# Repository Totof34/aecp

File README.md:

aecp
====

The project describes a electronic mapped car ignition
especialy for Panhard two cylindre

If you would have more information about this project please visit 
www.audiyofan.org

A link to the dedicated post 
http://www.audiyofan.org/forum/viewtopic.php?f=71&t=9221

PCB & schema are designed with Kicad

**********************************
*A new version called V4 in 2025*
**********************************

The new board in 2025

For the Gerber's file see the folder "aecp/source_kicad/gerber V4/"

all PCB Gerber files and 3D printing files from version 2025 grouped in the folder "aecp/manufacturing_files"

*******************************************************************

the new board uses a Atmega328 and usb link or a bluetooth module ( HC-05 or 06 )
to transmit some data to the PC

it's a Arduino Nano_V3

The idea comes from this site
http://a110a.free.fr/SPIP172/plan.php3

with this startpoint

And finally with a Nano V3.0 with a dedicated page here
http://a110a.free.fr/SPIP172/article.php3?id_article=142

But this project have some child too for exemple 
https://github.com/michelm63/AEMM
with a dedicated post here
http://motos-anglaises.com/phpBB3/viewtopic.php?f=3&t=28953

All the things we need is on this picture for the hardware,
and a car of course to use it !!

The prototype of the new board under construction and under kicad

With some parts 

The new version of the PCB for longtime test

You can select different curve with a box

To develop our electronic ignition, we create an new interface with a Nano_V3
to receive data from the Atmega328 and visualize the centrifugal advance curves and vacuum advance

This interface is designed under Processing IDE and the board is programmed with Arduino IDE
All the files available in subfolders

For the printed circuit board please see the source_kicad folder 
or the build folder for a made version

For the schema see below

for the rest, I suggest you to navigate into folders and open the pdf

The main code is explained through comments ( in French) in the ino file ( see Arduino folder )

Enjoy

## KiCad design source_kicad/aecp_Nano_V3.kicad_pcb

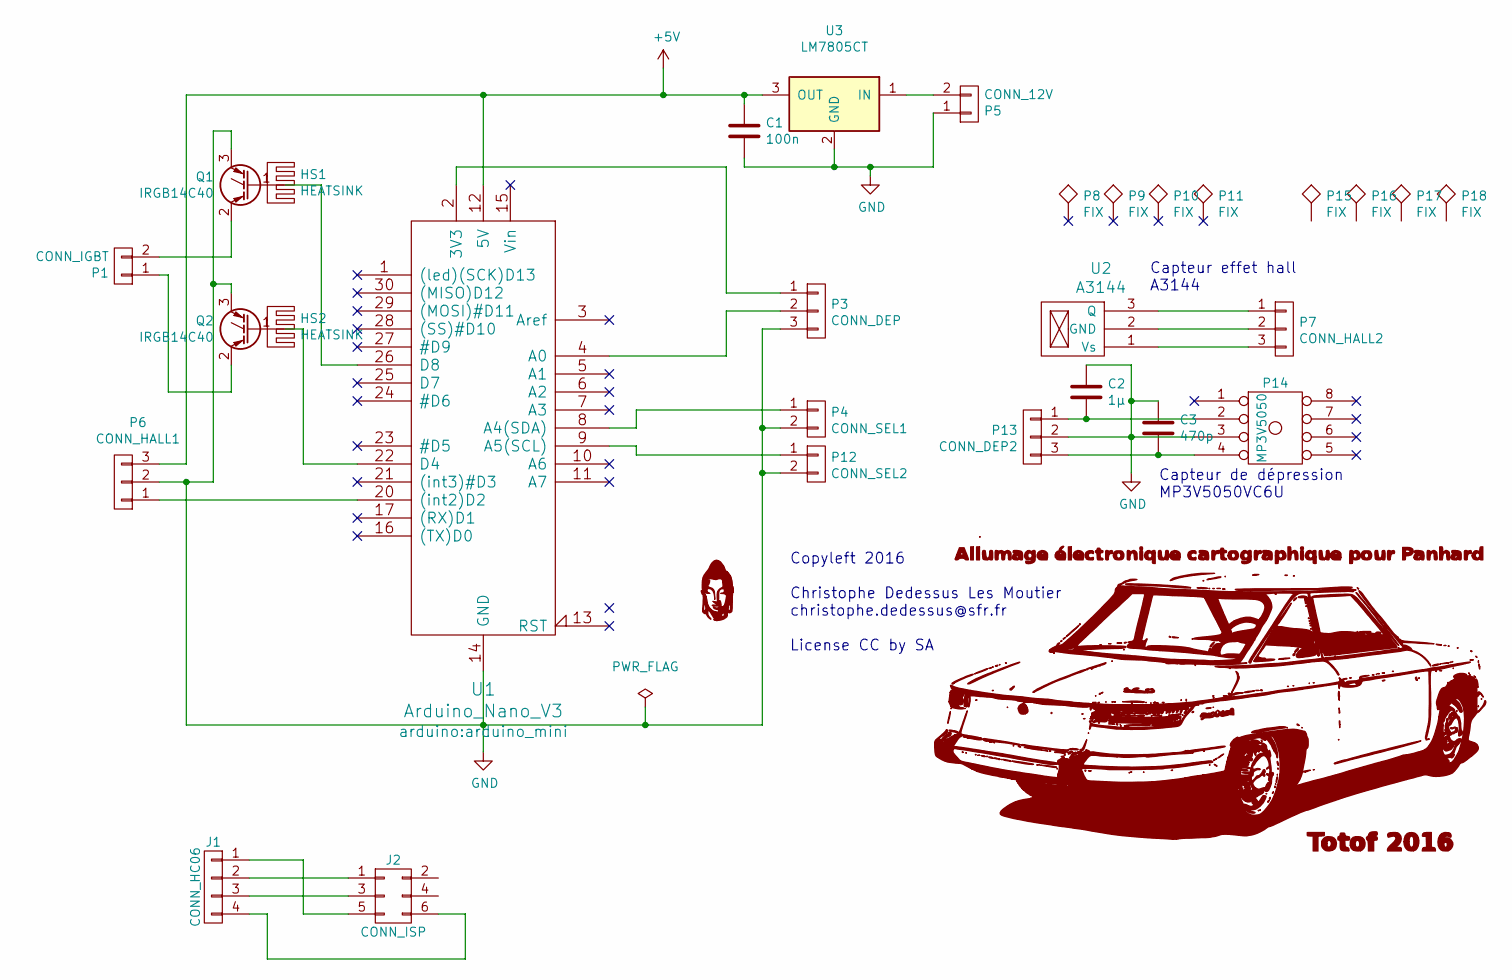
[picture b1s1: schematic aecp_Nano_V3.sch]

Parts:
C1: 100n; C_Rect_L7_W3.5_P5
C2: 1µ; C_Rect_L7_W3.5_P5
C3: 470p; C_Rect_L7_W3.5_P5
G1: Tete_budha
G2: 24CT; Panhard24CT
HS1, HS2: HEATSINK; Heatsink_Fischer_SK104-STC-STIC_35x13mm_2xDrill2.5mm
J1: CONN_HC06; pin_strip_4
J2: CONN_ISP; pin_strip_3x2
P1: CONN_IGBT; bornier2
P3: CONN_DEP; bornier3
P4: CONN_SEL1; bornier2
P5: CONN_12V; bornier2
P6: CONN_HALL1; bornier3
P7: CONN_HALL2; Socket_Strip_Straight_1x03
P8, P9, P10, P11: FIX; 1pin
P12: CONN_SEL2; bornier2
P13: CONN_DEP2; Socket_Strip_Straight_1x03
P14: MP3V5050; MP3V5050V
P15, P16, P17, P18: FIX; MountingHole_2.2mm_M2_Pad_Via
Q1, Q2: IRGB14C40; TO-220_Neutral123_Vertical_LargePads
U1: Arduino_Nano_V3; arduino_mini
U2: A3144; TO-92_Horizontal2_Inline_Narrow_Oval
U3: LM7805CT; TO-220_Neutral123_Vertical_LargePads

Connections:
+5V: C1.1, P6.3, U1.12 (5V), U3.3 (OUT)
GND: C1.2, C2.1, C3.1, P3.3, P4.2, P5.1, P6.2, P12.2, P13.2, P14.3, Q1.3 (E), Q2.3 (E), U1.14 (GND), U1.19 (GND), U3.2 (GND)
unnamed: C2.2, P13.1, P14.2
unnamed: C3.2, P13.3, P14.4
unnamed: J1.1, J2.5
unnamed: J1.2, J2.1
unnamed: J1.3, J2.3
unnamed: J1.4, J2.6
unnamed: P1.1, Q2.2 (C)
unnamed: P1.2, Q1.2 (C)
unnamed: P3.1, U1.2 (3V3)
unnamed: P3.2, U1.4 (A0)
unnamed: P4.1, U1.8 (A4(SDA))
unnamed: P5.2, U3.1 (IN)
unnamed: P6.1, U1.20 ((int2)D2)
unnamed: P7.1, U2.3 (Q)
unnamed: P7.2, U2.2 (GND)
unnamed: P7.3, U2.1 (Vs)
unnamed: P12.1, U1.9 (A5(SCL))
unnamed: Q1.1 (G), U1.26 (D8)
unnamed: Q2.1 (G), U1.22 (D4)

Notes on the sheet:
Copyleft 2016 Christophe Dedessus Les Moutier christophe.dedessus@sfr.fr License CC by SA
Capteur de dépression MP3V5050VC6U
Capteur effet hall A3144

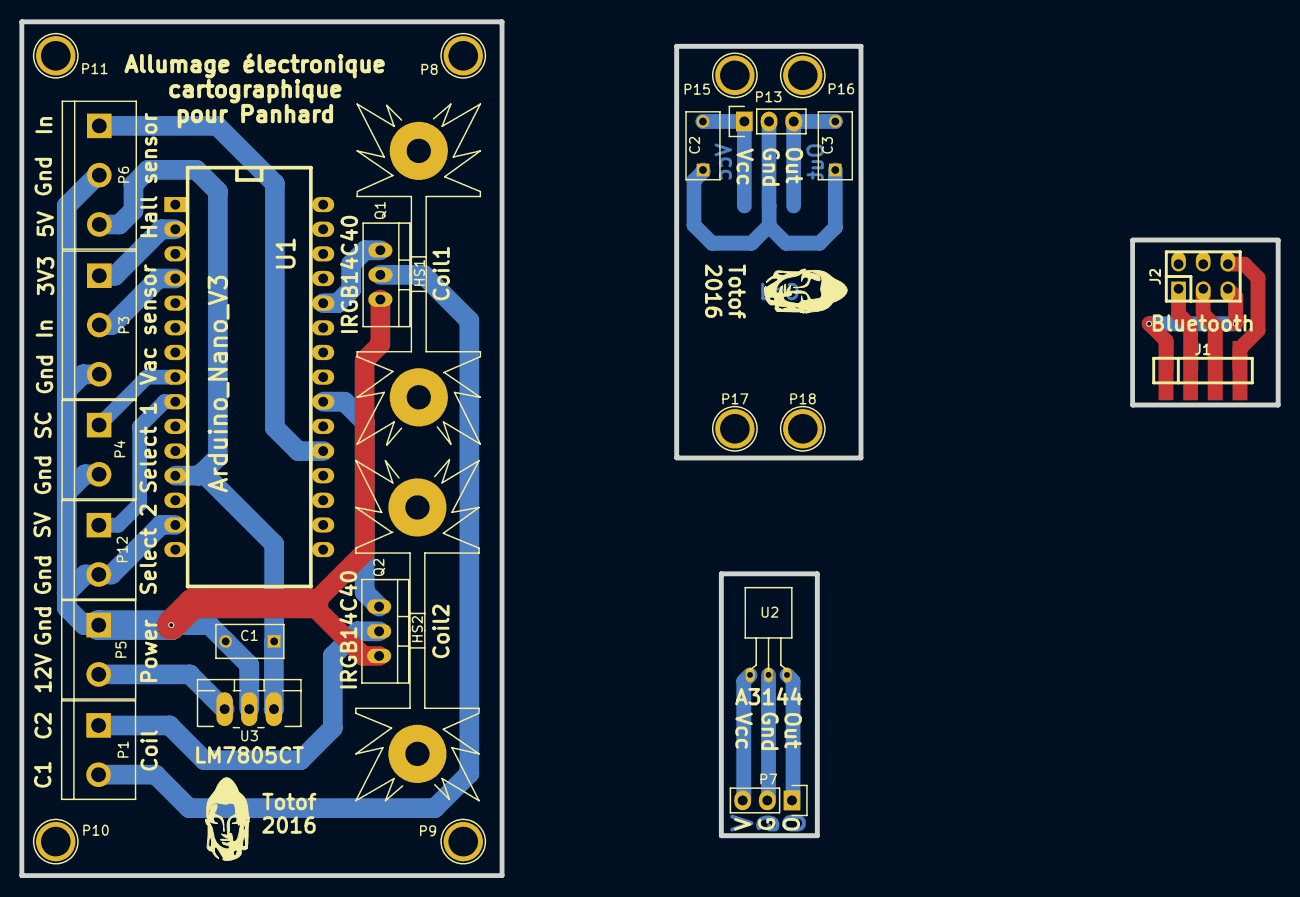
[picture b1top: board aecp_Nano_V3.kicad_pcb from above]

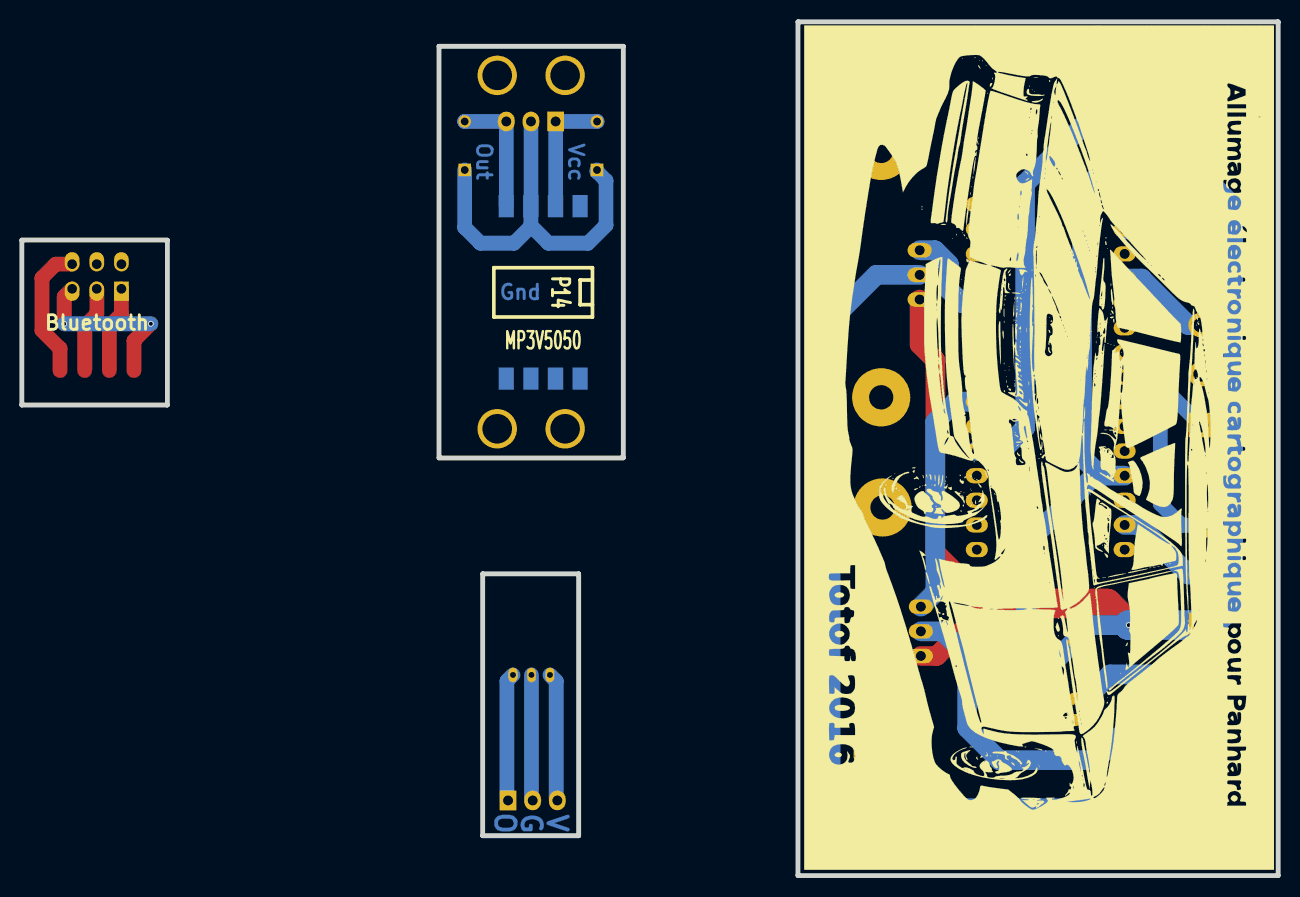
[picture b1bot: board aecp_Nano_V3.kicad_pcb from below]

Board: 2 copper layers, 129.5 x 88.0 mm, 32 parts (2 on the bottom side), 21 nets.

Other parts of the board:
G1#2: Tete_budha

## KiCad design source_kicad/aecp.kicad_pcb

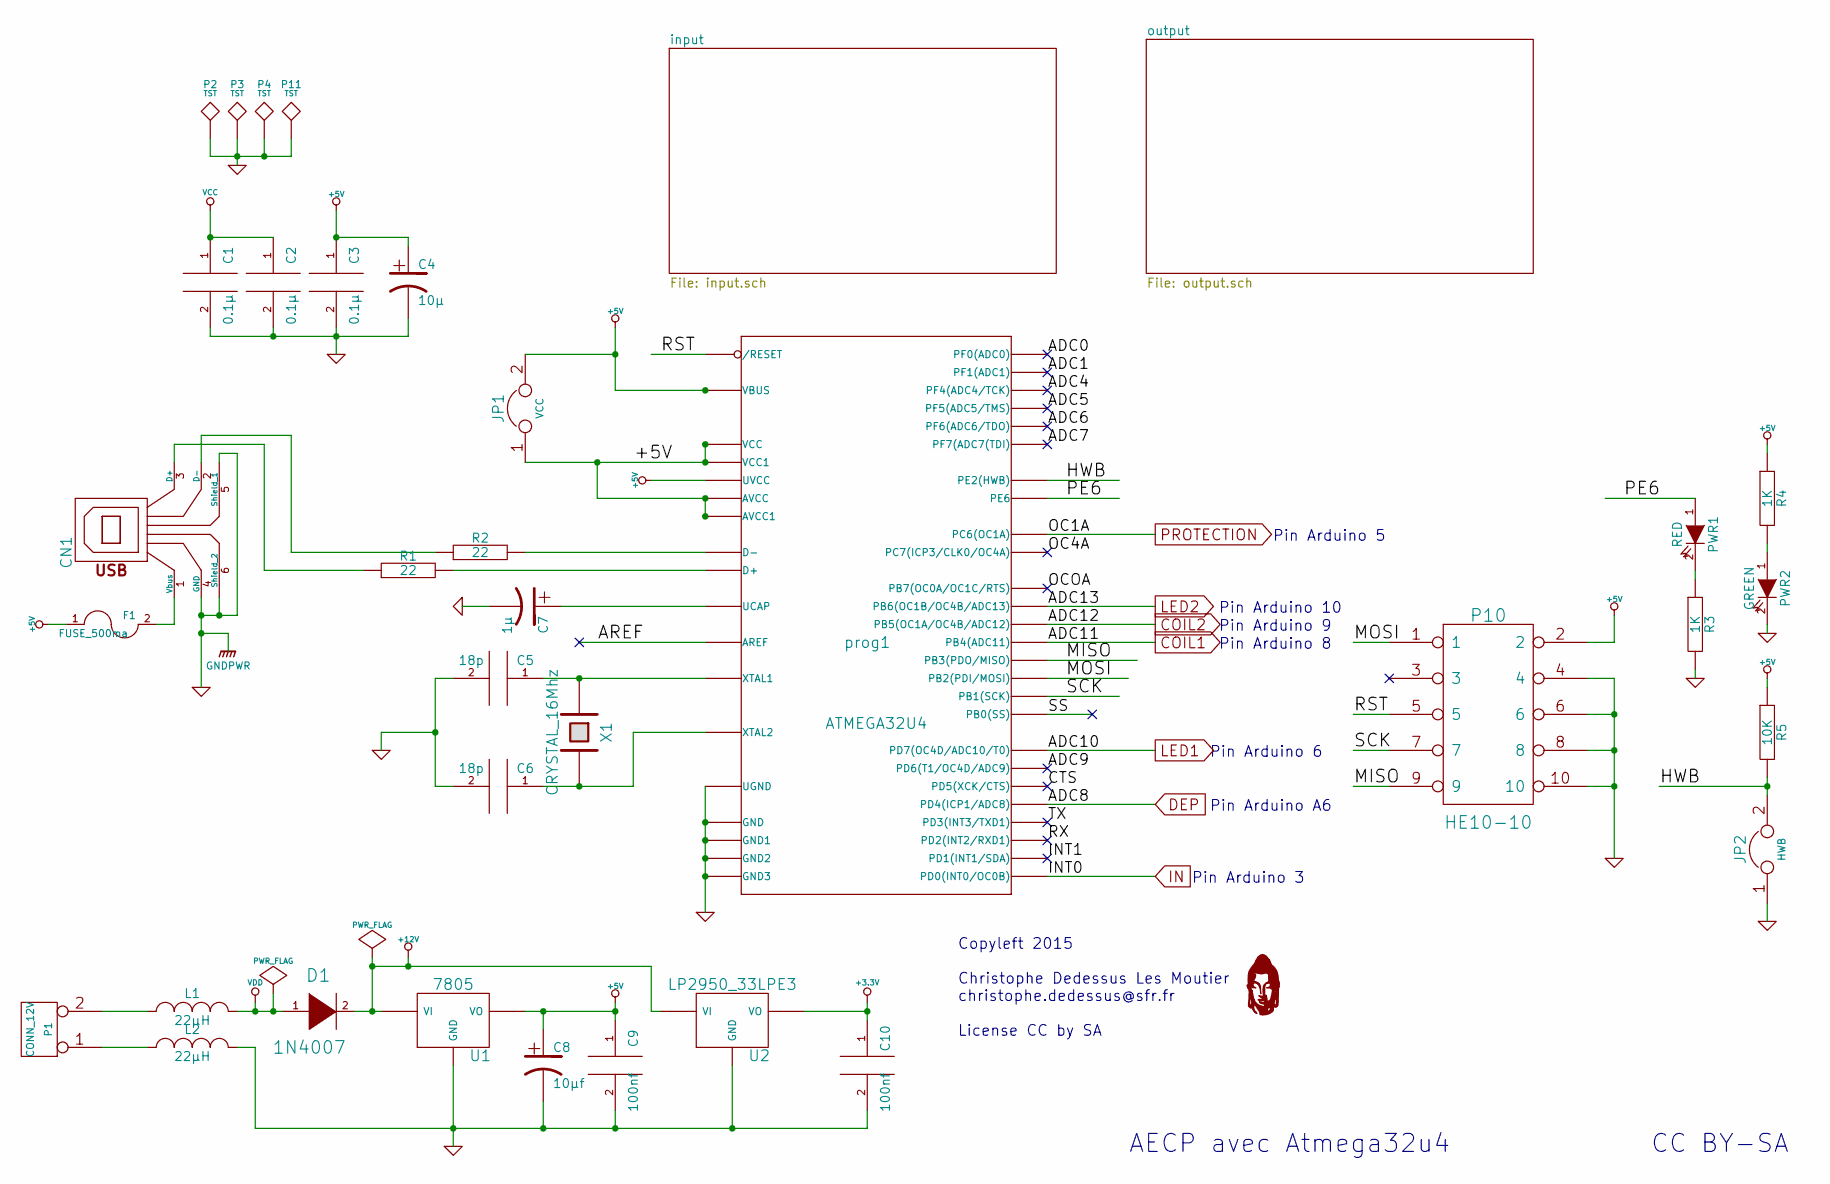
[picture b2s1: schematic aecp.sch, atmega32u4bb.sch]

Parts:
C1, C2, C3: 0.1µ; C2
C4: 10µ; C1V8
C5, C6: 18p; C1
C7: 1µ; C2
C8: 10µf; C1V8
C9, C10: 100nf; C2
CN1: USB_1; USB_B
D1: 1N4007; D4
F1: FUSE_500ma; Fuseholder5x20_horiz_SemiClosed_Casing10x25mm
G1: LOGO; Tete_boudha
JP1: VCC; Pin_Header_Straight_1x02
JP2: HWB; Pin_Header_Straight_1x02
L1, L2: 22µH; R4-LARGE_PADS
P1: CONN_12V; bornier2
P2, P3, P4, P11: TST; 1pin
P10: HE10-10; Socket_Strip_Straight_2x05
PWR1: RED; LED-5MM
PWR2: GREEN; LED-5MM
R1, R2: 22; R4-LARGE_PADS
R3, R4: 1K; R4-LARGE_PADS
R5: 10K; R4-LARGE_PADS
U1: 7805; LM78XXV
U2: LP2950_33LPE3; TO-92-Free-rugged
X1: CRYSTAL_16Mhz; Crystal_HC49-U_Vertical
prog1: ATMEGA32U4; TQFP-44

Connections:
+3.3V: C10.1, U2.3 (VO); also elsewhere on the board
+5V: C3.1, C4.1, C8.1, C9.1, F1.1, JP1.1, JP1.2, P10.2, R4.1, R5.1, U1.VO, prog1.2 (UVCC), prog1.7 (VBUS), prog1.14 (VCC), prog1.24 (AVCC), prog1.34 (VCC1), prog1.44 (AVCC1); also elsewhere on the board
/ADC0: prog1.41 (PF0(ADC0))
/ADC1: prog1.40 (PF1(ADC1))
/ADC4: prog1.39 (PF4(ADC4/TCK))
/ADC5: prog1.38 (PF5(ADC5/TMS))
/ADC6: prog1.37 (PF6(ADC6/TDO))
/ADC7: prog1.36 (PF7(ADC7(TDI))
/ADC9: prog1.26 (PD6(T1/OC4D/ADC9))
/AREF: prog1.42 (AREF)
/CTS: prog1.22 (PD5(XCK/CTS))
/HWB: JP2.2, R5.2, prog1.33 (PE2(HWB))
/INT1: prog1.19 (PD1(INT1/SDA))
/MISO: P10.9, prog1.11 (PB3(PDO/MISO))
/MOSI: P10.1, prog1.10 (PB2(PDI/MOSI))
/OC4A: prog1.32 (PC7(ICP3/CLK0/OC4A))
/OCOA: prog1.12 (PB7(OC0A/OC1C/RTS))
/PE6: PWR1.1 (A), prog1.1 (PE6)
/RST: P10.5, prog1.13 (/RESET)
/RX: prog1.20 (PD2(INT2/RXD1))
/SCK: P10.7, prog1.9 (PB1(SCK))
/SS: prog1.8 (PB0(SS))
/TX: prog1.21 (PD3(INT3/TXD1))
COIL1: prog1.28 (PB4(ADC11)); also elsewhere on the board
COIL2: prog1.29 (PB5(OC1A/OC4B/ADC12)); also elsewhere on the board
DEP: prog1.25 (PD4(ICP1/ADC8)); also elsewhere on the board
GND: C1.2, C2.2, C3.2, C4.2, C5.2, C6.2, C7.2, C8.2, C9.2, C10.2, CN1.4 (GND), CN1.5 (Shield_1), CN1.6 (Shield_2), JP2.1, L2.2, P2.1, P3.1, P4.1, P10.4, P10.6, P10.8, P10.10, P11.1, PWR2.2 (K), R3.2, U1.GND, U2.2 (GND), prog1.5 (UGND), prog1.15 (GND), prog1.23 (GND1), prog1.35 (GND2), prog1.43 (GND3); also elsewhere on the board
IN: prog1.18 (PD0(INT0/OC0B)); also elsewhere on the board
LED1: prog1.27 (PD7(OC4D/ADC10/T0)); also elsewhere on the board
LED2: prog1.30 (PB6(OC1B/OC4B/ADC13)); also elsewhere on the board
unnamed: C5.1, X1.1, prog1.17 (XTAL1)
unnamed: C6.1, X1.2, prog1.16 (XTAL2)
unnamed: C7.1, prog1.6 (UCAP)
unnamed: CN1.1 (Vbus), F1.2
unnamed: CN1.2 (D-), R2.1
unnamed: CN1.3 (D+), R1.1
unnamed: L1.1, P1.2 (PM)
unnamed: L2.1, P1.1
unnamed: PWR1.2 (K), R3.1
unnamed: PWR2.1 (A), R4.2
unnamed: R1.2, prog1.4 (D+)
unnamed: R2.2, prog1.3 (D-)
PROTECTION: prog1.31 (PC6(OC1A)); also elsewhere on the board
VDD: D1.1 (A), L1.2

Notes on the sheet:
AECP avec Atmega32u4
CC BY-SA
Copyleft 2015 Christophe Dedessus Les Moutier christophe.dedessus@sfr.fr License CC by SA
Pin Arduino 5
Pin Arduino A6
Pin Arduino 3
Pin Arduino 6
Pin Arduino 10
Pin Arduino 9
Pin Arduino 8

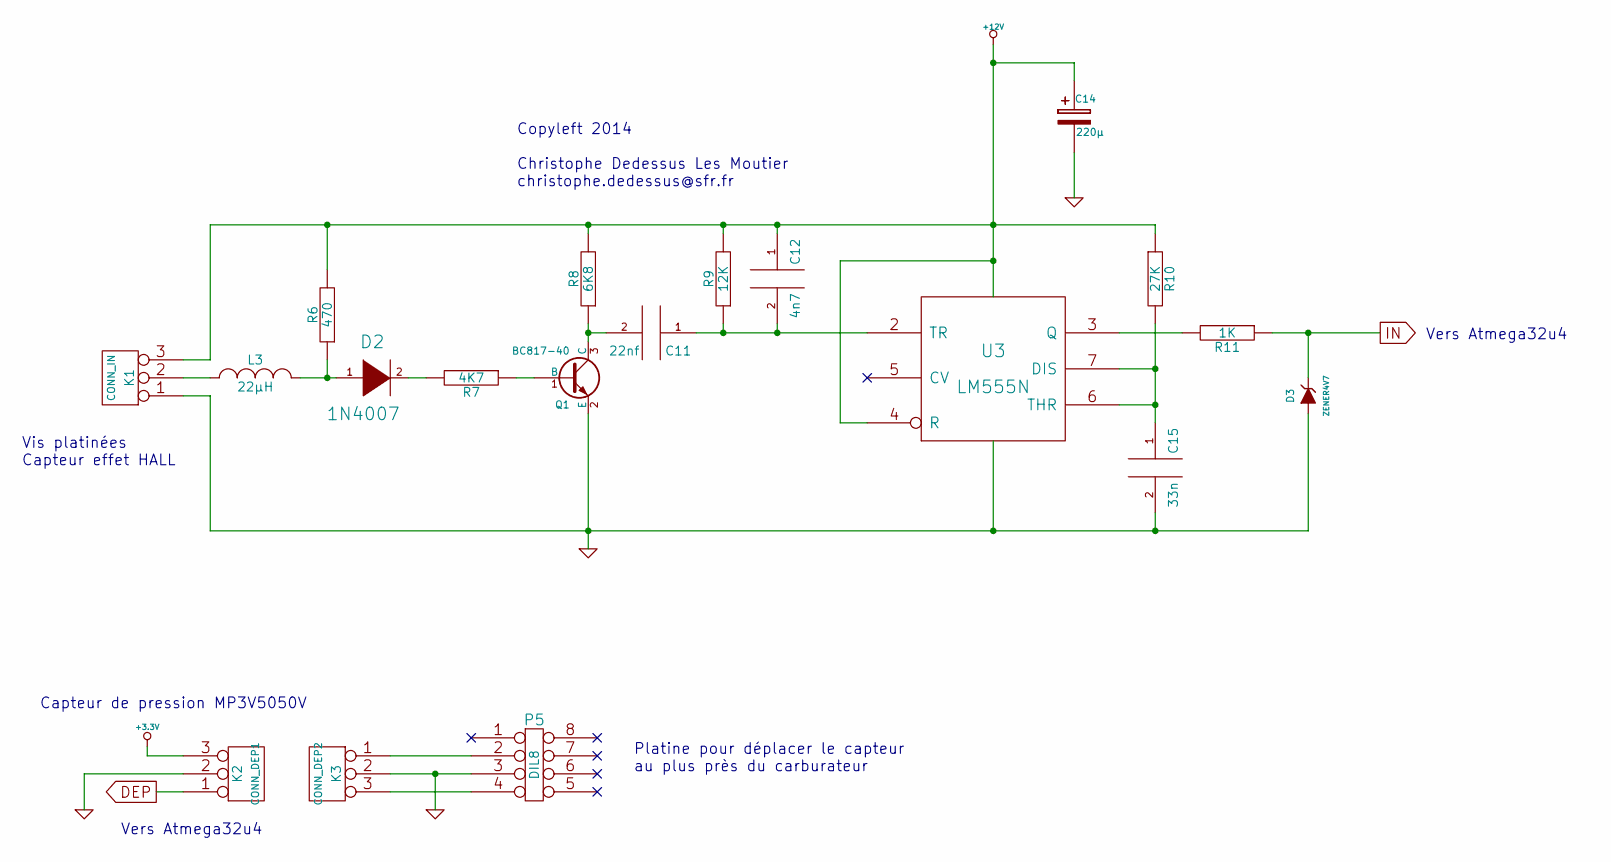
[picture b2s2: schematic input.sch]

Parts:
C11: 22nf; C2
C12: 4n7; C2
C14: 220µ; C2V8
C15: 33n; C2
D2: 1N4007; D4
D3: ZENER4V7; D4
K1: CONN_IN; bornier3
K2: CONN_DEP1; bornier3
K3: CONN_DEP2; SIL-3
L3: 22µH; R4-LARGE_PADS
P5: DIL8; DIP-8__300_ELL
Q1: BC817-40; TO-92-Free-rugged
R6: 470; R4-LARGE_PADS
R7: 4K7; R4-LARGE_PADS
R8: 6K8; R4-LARGE_PADS
R9: 12K; R4-LARGE_PADS
R10: 27K; R4-LARGE_PADS
R11: 1K; R4-LARGE_PADS
U3: LM555N; DIP-8__300_ELL

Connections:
+3.3V: K2.3; also elsewhere on the board
DEP: K2.1; also elsewhere on the board
GND: C14.2, C15.2, D3.1 (A), K1.1, K2.2 (PM), K3.2 (PM), P5.3, Q1.2 (E), U3.1 (GND); also elsewhere on the board
IN: D3.2 (K), R11.1; also elsewhere on the board
unnamed: C11.1, C12.2, R9.1, U3.2 (TR)
unnamed: C11.2, Q1.3 (C), R8.1
unnamed: C15.1, R10.2, U3.6 (THR), U3.7 (DIS)
unnamed: D2.1 (A), L3.2, R6.1
unnamed: D2.2 (K), R7.2
unnamed: K1.2 (PM), L3.1
unnamed: K3.1, P5.2
unnamed: K3.3, P5.4
unnamed: Q1.1 (B), R7.1
unnamed: R11.2, U3.3 (Q)

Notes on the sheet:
Copyleft 2014 Christophe Dedessus Les Moutier christophe.dedessus@sfr.fr
Vis platinées Capteur effet HALL
Vers Atmega32u4
Capteur de pression MP3V5050V
Platine pour déplacer le capteur au plus près du carburateur

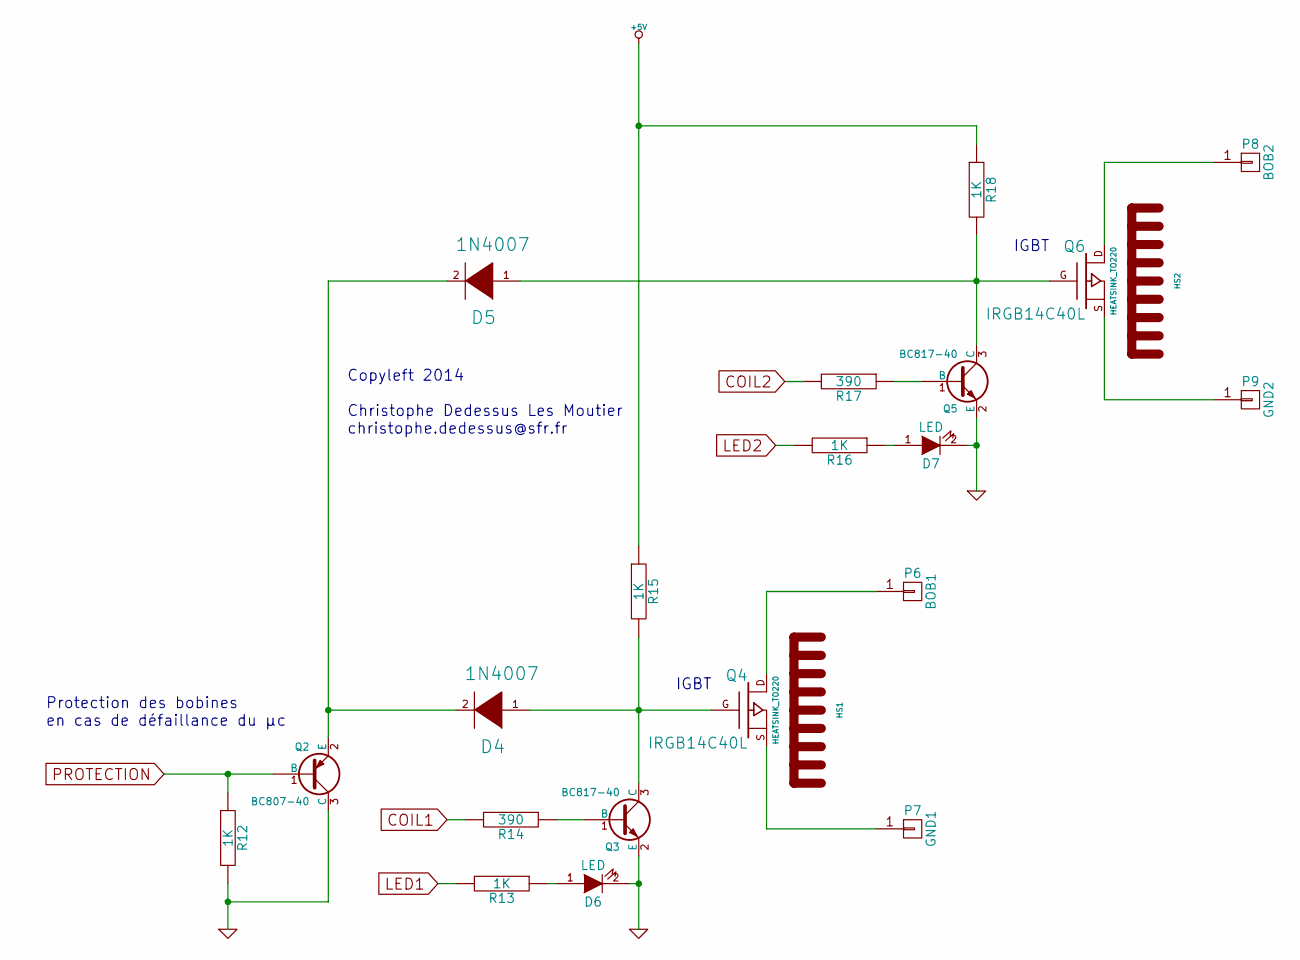
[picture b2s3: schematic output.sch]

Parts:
D4, D5: 1N4007; D4
D6, D7: LED; LED-5MM
HS1, HS2: HEATSINK_TO220; Heatsink_Fischer_SK104-STC-STIC_35x13mm_2xDrill2.5mm
P6: BOB1; Pin_Header_Straight_1x01
P7: GND1; Pin_Header_Straight_1x01
P8: BOB2; Pin_Header_Straight_1x01
P9: GND2; Pin_Header_Straight_1x01
Q2: BC807-40; TO-92-Free-rugged
Q3, Q5: BC817-40; TO-92-Free-rugged
Q4, Q6: IRGB14C40L; TO-220_FET-GDS_Vertical_LargePads
R12, R13, R15, R16, R18: 1K; R4-LARGE_PADS
R14, R17: 390; R4-LARGE_PADS

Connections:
+5V: R15.1, R18.1; also elsewhere on the board
COIL1: R14.2; also elsewhere on the board
COIL2: R17.2; also elsewhere on the board
GND: D6.2 (K), D7.2 (K), Q2.3 (C), Q3.2 (E), Q5.2 (E), R12.2; also elsewhere on the board
LED1: R13.2; also elsewhere on the board
LED2: R16.2; also elsewhere on the board
unnamed: D4.1 (A), Q3.3 (C), Q4.G, R15.2
unnamed: D4.2 (K), D5.2 (K), Q2.2 (E)
unnamed: D5.1 (A), Q5.3 (C), Q6.G, R18.2
unnamed: D6.1 (A), R13.1
unnamed: D7.1 (A), R16.1
unnamed: P6.1, Q4.D
unnamed: P7.1, Q4.S
unnamed: P8.1, Q6.D
unnamed: P9.1, Q6.S
unnamed: Q3.1 (B), R14.1
unnamed: Q5.1 (B), R17.1
PROTECTION: Q2.1 (B), R12.1; also elsewhere on the board

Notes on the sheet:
Copyleft 2014 Christophe Dedessus Les Moutier christophe.dedessus@sfr.fr
IGBT
Protection des bobines en cas de défaillance du µc

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
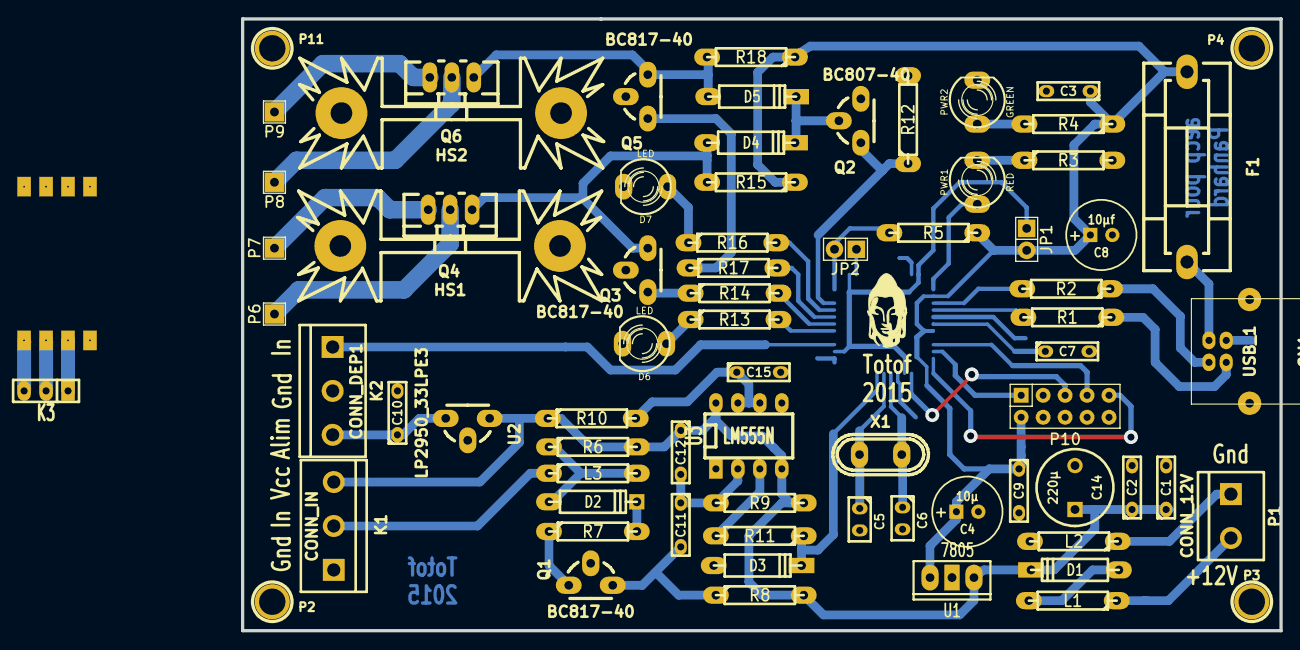
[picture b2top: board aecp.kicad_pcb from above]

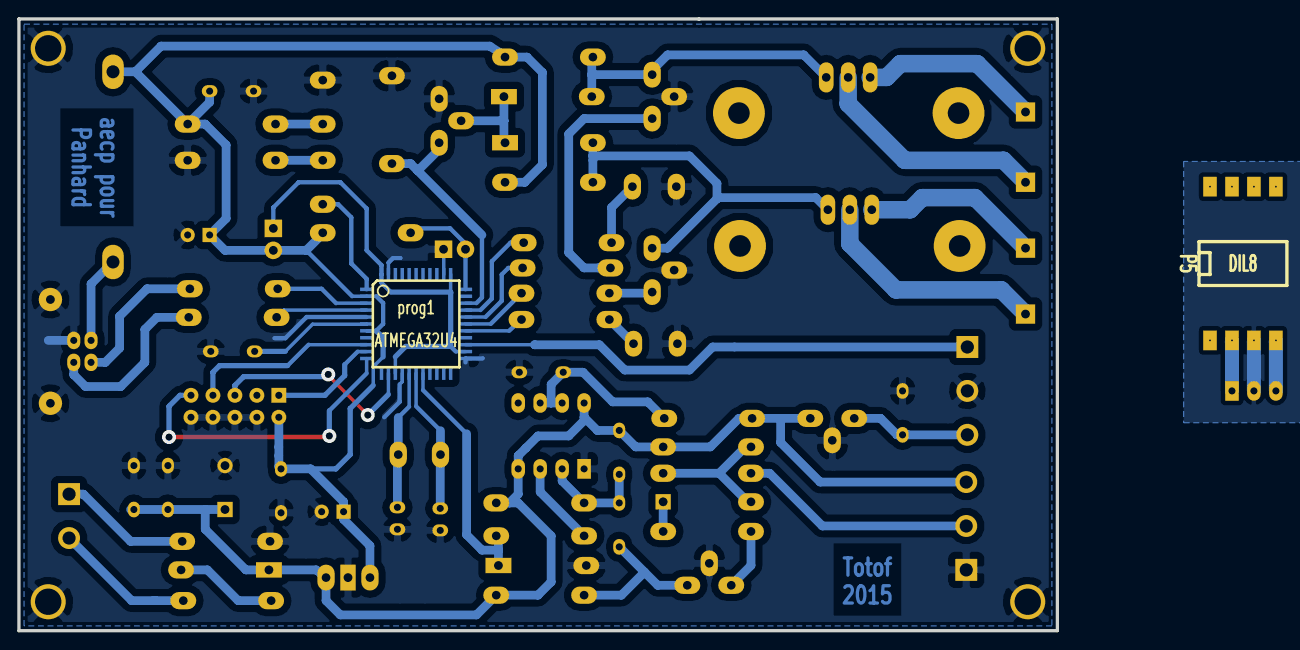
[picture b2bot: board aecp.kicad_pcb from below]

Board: 2 copper layers, 120.1 x 70.8 mm, 76 parts (2 on the bottom side), 51 nets.

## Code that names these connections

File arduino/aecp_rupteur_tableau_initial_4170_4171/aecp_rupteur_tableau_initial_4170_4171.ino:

// Version pour moteur Panhard, 2 cylindre avec emploi de la tete de delco d'origine
// vidée des masselotes de l'avance centrifuge et la capsule de dépression déconnectée
//
// 25/10/2014
// Test de la vitesse de rotation et capture de la valeur de dépression issu du capteur
// vérifié avec un banc Souriau
// 
// 10/01/2015
// Test de conformité des calculs des délais
// et rectification des formules du tableau initial précédement erronné
// Ok à la date du 11/01/2015
// 
// 13/10/2015
// Tet de conformité de la vitese décodée et du bon délai d'avance en fonction
// du meme tableau 
// Calibration de la plage du capteur de dépreion 
// Ok à la date du 13/01/2015

// Ok à la date du 24/01/2015
// Test affichage sous Processing OK et Validation des délais ainsi que le taux d'erreur global
// qui est générer par le µc pour tout les calculs
// validation aussi du transfert des données vers Processing et l'IHM

// Ci-desous le deux principales lignes de code qui détermine l'allure des courbes destinées aux moteur Panhard
// celle-ci est pour un allumeur AC4114A pour moteur M8N qui équipe les 24 et 17 de la marque
// les deux tableaux sont remplis au départ d'un relevé manuel des courbes construxteur
// le premier est constitué par les degrés d'avance centrifuge additionné de l'avance statique

// L'avance statique est de 4.5 dents d'avance statique côté volant moteur à partir de 0 T/min X10 pour avoir un entier
// Degrés à convertir en degrés allumeur ( 104 dents pour 360°), (360/104)*4.5, ce qui donne ici 156

// Le second comprend les vitesses en tours allumeur soit tours moteur divisé par 2

volatile int Advance[11]= {156,156,166,181,196,201,206,206,206,206,206  }; // en 1/10 de degrés d'avance allumeur à partir de 0 T/min,soit avec l'avance statique];
volatile int Speed[11] = {0,540,1000,1400,1800,1900,2000,2080,2100,3000,3500  }; // Vitesse de rotation en tour allumeur;

// Début du code source

const int MIN_RPM = 0; // La vitesse de départ soit 0 tour par min
const int MAX_RPM = 3500; // La vitesse maximum ou ligne rouge
const int STEP_RPM = 20; // Le pas pour faire croitre la vitesse dans le tableau
const int MAX_INDEX = 175; // L'index maximum sert à calculer la taille du tableau, 3500/20
const int DWELL = 3000;
const int COIL1 = 8;
const int LED1 = 6;
const int LED2 = 10;
const int COIL2 = 9;
const int PROTECT = 5; // Sortie pour bloquer les grilles des IGBT
const int SENSOR1 = 3; // Capteur de PMH
//const int SENSOR2 = 4; // Capteur de vitesse lente

// Définition de constante pour différentes vitesses de conversion Analogique => Numérique
const unsigned char PS_16 = (1 << ADPS2);
const unsigned char PS_32 = (1 << ADPS2) | (1 << ADPS0);
const unsigned char PS_64 = (1 << ADPS2) | (1 << ADPS1);
const unsigned char PS_128 = (1 << ADPS2) | (1 << ADPS1) | (1 << ADPS0); 

bool triggered = false;
volatile unsigned long elapsedtime = 0;
volatile unsigned long conversiontime = 0;
volatile unsigned long conversiontime_global = 0;
volatile unsigned long lastDuration = 0;
volatile unsigned long finaldelay = 0;
volatile unsigned long engine_rpm;            // Vitesse courante
volatile long lastDelay = 0;
volatile int Depvalue = 0; // Lecture du capteur de depression
int Depvaluemaped = 0 ; // Transformation des unités
volatile unsigned short currentIndex = 0;
volatile unsigned long delaytime = 0;

volatile float slope[11];
volatile float intercept[11];

volatile unsigned long RPMS[MAX_INDEX];
volatile unsigned long DELAYDEP[MAX_INDEX];
volatile unsigned long DELAYS[MAX_INDEX];

volatile long map_rpm = 1;
volatile int milli_delay = 0;
volatile int micro_delay = 0;
volatile int map_pressure = 0;
volatile int cmap_pressure = 0; // Cmap pour avoir une échelle qui va de 0 à 15 degrés

volatile int pressure_axis[15] = {70, 80, 90, 100, 110, 120, 130, 140, 150, 160, 170, 180, 190, 200, 210};  // 15

// manifold pressure averaging array
const int numReadings = 5;                    // Taille du tableeau pour moyenner la pression
volatile int readings[numReadings];                     // Tableau de vitesses lues
volatile int current_index = 0;                         // Index de la vitesse courante lue
volatile unsigned long total = 0;                       // La somme des vitesses lues
volatile unsigned int manifold_pressure = 0;            // Moyenne de départ des pressions
volatile int map_pressure_kpa;

//rpm averaging array
const int num_rpm_readings = 10;               // Taille du tableeau pour moyenner la vitesse courante
volatile int rpm_readings[num_rpm_readings];   // Tableau de vitesses lues
volatile int current_index_rpm = 0;            // Index de la vitesse courante lue
volatile unsigned long rpm_total = 0;          // La somme des vitesses lues
volatile unsigned int engine_rpm_average = 0;  // Moyenne de départ des vitesses

// Tableau pour sauver des données temporelles
unsigned long start_times;
unsigned long start_times_global;
unsigned long stop_times;
unsigned long stop_times_global;
int code_delay = 100; // cette valeur doit correspondre au temps que prend la routine d'interrution du capteur de rotation

/// Construction du tableau des délais au départ de la vitesse de rotation et des valeurs d'avance
/// La ligne rouge est MAX_RPM
void calculateArrayValues()
{
  float startRPM = MIN_RPM; // Usage d'un double pour accroitre la précision des calculs
  
  int CALC_RPM = 0; // Pour créer le tableau
  int hallAdvance = 180; // On assimile le position du capteur de rotation à 180° du point mort haut

  for(int x = 1; x <=11; x++)
  {
        
    slope[x] = abs(Advance[x] - Advance[x-1])/float((Speed[x] - Speed[x-1])*10); // La fonction pour calculer l'avance linéaire est y = mx+b ou m = (y2-y1)/(x2-x1)
        
    intercept[x] = (Advance[x-1]*0.1)-((Speed[x-1]*slope[x]));  // Calcule la valeur de b d'après la formule précédente
    
    CALC_RPM = Speed[x-1];
    // Construis le tableau avec un pas de 20 T/min 
    for(int i = (Speed[x-1]/STEP_RPM); i < (Speed[x]/STEP_RPM); i++)
    {

      float usPerDegree = 60000000 / CALC_RPM / 360;  // 60000000 car tour allumeur
      float advance = 0;
      advance = (CALC_RPM * slope[x]) + intercept[x]; // Utilise notre fonction pour calculer l'avance

      unsigned long advanceDelay;


      advanceDelay = ((hallAdvance - advance) * usPerDegree) - DWELL - code_delay ; //calcule le temps a appliquer (delai) entre le signal et l'étincelle


      RPMS[i] = usPerDegree * 180;// * 180 car essai avec tete de delco
      
      DELAYS[i] = advanceDelay;
      
      DELAYDEP[i] = usPerDegree; // Lorsqu'on est sur une vitesse de rotation, on multiplie le délai par degré par le "mappage" de la valeur du capteur

      CALC_RPM += STEP_RPM; // Incrémente de 10 T/min à chaque itération


    }
  }
}



/// Applique les propriétés au départ (1 seule fois) puis attache les interruptions
void setup()
{
  pinMode(COIL1, OUTPUT); // initialise en sortie la patte qui alimente la bobine 1
  pinMode(LED1, OUTPUT);  // initialise en sortie la patte qui alimente la Led 1
  pinMode(COIL2, OUTPUT);
  pinMode(LED2, OUTPUT);
  pinMode(PROTECT, OUTPUT);
  pinMode(SENSOR1, INPUT);
  //pinMode(SENSOR2, INPUT);
  Serial.begin(115200);

  digitalWrite(COIL1, HIGH);
  digitalWrite(COIL2, HIGH);
  digitalWrite(PROTECT, HIGH); // Débloque la grille de l'IGBT

  calculateArrayValues();
  
  // Initialise les conversions A=>N
  ADCSRA &= ~PS_128;  // Enlève le bits mis d'originr par Arduino
  
  // On peut ici choisir son diviseur d'horloge.
  // PS_16, PS_32, PS_64 or PS_128
  ADCSRA |= PS_16;    
  // Choisir votre diviseur à PS_16 est la vitesse la plus rapide 

 

}

void editcourbe(){
  for(int i = 0; i < 175; i++)
    {    
    Serial.print(i*20);
    Serial.print(",");
    Serial.print(DELAYS[i]);
    Serial.print(",");
    Serial.println(DELAYDEP[i]);
    }
}

void demo(){
  for(int i = 1; i < 175; i++){
    Serial.print("V");
    Serial.print(",");
    Serial.print(i*20);
    Serial.print(",");
    Serial.print("0");
    Serial.print(",");
    Serial.print(DELAYS[i]);
    Serial.print(",");
    Serial.print(DELAYDEP[i]);
    Serial.print(",");
    Serial.print("0");
    Serial.println(",");
    delay(100);
  }
}


/// Si on capte un signal sur l'entrée on récupère le délai et on actionne la bobine.
void loop()
{
 
   //editcourbe();
       
   demo();

}

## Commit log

2015-01-27 First commit to create project
2015-01-28 Add new version of the software (1350x690) with selectionable curve and the ino file to calculate the other curve
2015-03-26 New version of software & source-code for hardware
2016-07-02 New update with an Arduino Nano_V3 as board , 2016 project
2016-07-02 New schematic
2016-07-03 Add new picture of the board
2016-07-04 New version of source code for Processing & Arduino
2016-07-06 Add new schématic and new board under Kicad, also a new version under Arduino
2016-07-07 Add a pictue of the curve selector and add a new ino file
2016-07-07 A bug with a picture of the new board corrected
2016-07-08 Add new version of source code for Processing & Arduino
2016-07-09 New version of aecp under processing with the motor M10S
2016-07-10 Add new version of source code with the type of motor
2016-07-10 Bug between M10S & M8S corrected
2016-07-17 Add new version of Arduino's code
2016-10-16 New version of the PCB
2016-10-22 New PCB version
2016-10-25 Last version of PCB with gerber files
2016-11-18 Bug corrected in the PCB
2016-11-18 The new version aecp_Nano_V3 is ready for longtime test
2016-11-19 Add picture of the new PCB, soldering and mounting
2016-11-19 Bug corrected under processing
2016-11-25 New IHM under Processing 3.2.3
2016-12-25 New version of code under Arduino
2017-03-02 New program version with bluetooth connexion
2017-03-02 Github of Michel Martinet added
2017-03-13 New version for Arduino and Processing 3.3 with bluetooth
2017-03-19 New version of Android program under Processing
2017-03-26 New source file for kicad with bluetooth adaptator
2017-04-17 New version of android software
2017-04-18 New version for Arduino and Processing
2017-07-09 Add new picture for the hardware and corrected source code for Arduino
2017-07-09 Add corrected source code for processing
2017-07-09 Add bluetooth in the readme
2017-07-09 New version of android application and dummy for arduino
2017-09-04 New version of android application
2025-07-23 Add new file with 2025 version called aecp_V4
2025-07-23 Edit Readme file
2025-07-23 Edit readme.md
2025-08-31 Add manufacturing files of the complete 2025 version
2026-06-24 Add new files for Processing 4 & android 12 application
2026-06-30 Add Android 12.5 version
